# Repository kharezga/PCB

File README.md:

# My PCBs
This repository contains sereveral PCB board that I've design for use in the Formula Student racecar. In addition to PCB designs, the repository also includes 3D models of some of their housings.

## 🚨 Tractive System Active Light (TSAL) module 🚨
According to the Formula Student Rules 2022, the Tractive System Active Light (TSAL) is a safety feature that must be implemented in all electric vehicles participating in the competition. Whole project of the TSAL can be found in this repository, including PCB layout and scheme. 

### Overview
The TSAL must be based on the voltage level of the High Voltage (HV) battery or the voltage level of the motor controller, and it should indicate whether the tractive system is active or not.

The TSAL should be mounted on the rear of the vehicle and must be clearly visible from the rear of the vehicle during both day and night conditions. The light should be red or yellow and must flash at a frequency between 1Hz and 4Hz.

During normal operation, the TSAL should remain on steadily to indicate that the tractive system is active. When the vehicle is in an emergency or shutdown state, the TSAL should flash at a higher frequency between 4Hz and 10Hz to indicate that the tractive system is inactive.

## Ready-to-Run Sound and Autonomous System Status Indicators module
In this repository there is also a project containing a module for ready-to-run-sound and ASSI safety systems.

### 🔊 Ready-to-Run Sound 🔊
According to the Formula Student Rules 2022, Ready-to-Run Sound (RtRS) is a safety feature that must be implemented in all electric vehicles participating in the competition.

The purpose of the RtRS is to alert pedestrians and other drivers of the presence of an electric vehicle, which can be difficult to hear due to its quiet operation. The sound must be continuous, with a minimum sound pressure level of 55dB(A) and a maximum of 75dB(A) measured at a distance of 2 meters from the vehicle in all directions.

The RtRS must be activated when the vehicle is in Ready-to-Run mode, which means the vehicle is ready to move and all systems are operational. The sound should be automatically turned off when the vehicle is not in Ready-to-Run mode or is turned off.

### 🤖 Autonomous System Status Indicators 🤖
According to the Formula Student Rules 2022, the Autonomous System Status Indicators (ASSI) module is a safety feature that must be implemented in all autonomous vehicles participating in the competition.

The ASSI module is responsible for providing visual and audible feedback on the status of the autonomous system to the vehicle occupants, other drivers, and pedestrians. The module must be integrated into the vehicle's user interface or dashboard and should display the following information:

+ Autonomous System Status: The module must display the status of the autonomous system, indicating whether it is active or inactive.
+ System Health Status: The module must display the health status of the autonomous system, indicating whether the system is functioning correctly or not.
+ System State: The module must display the current state of the autonomous system, indicating whether the system is in calibration mode, initialization mode, or autonomous driving mode.

In addition to the visual feedback, the ASSI module must also provide audible feedback to alert the vehicle occupants and pedestrians of any critical issues related to the autonomous system. The audible feedback must be distinct and easily identifiable from any other sounds in the vehicle or surrounding environment.

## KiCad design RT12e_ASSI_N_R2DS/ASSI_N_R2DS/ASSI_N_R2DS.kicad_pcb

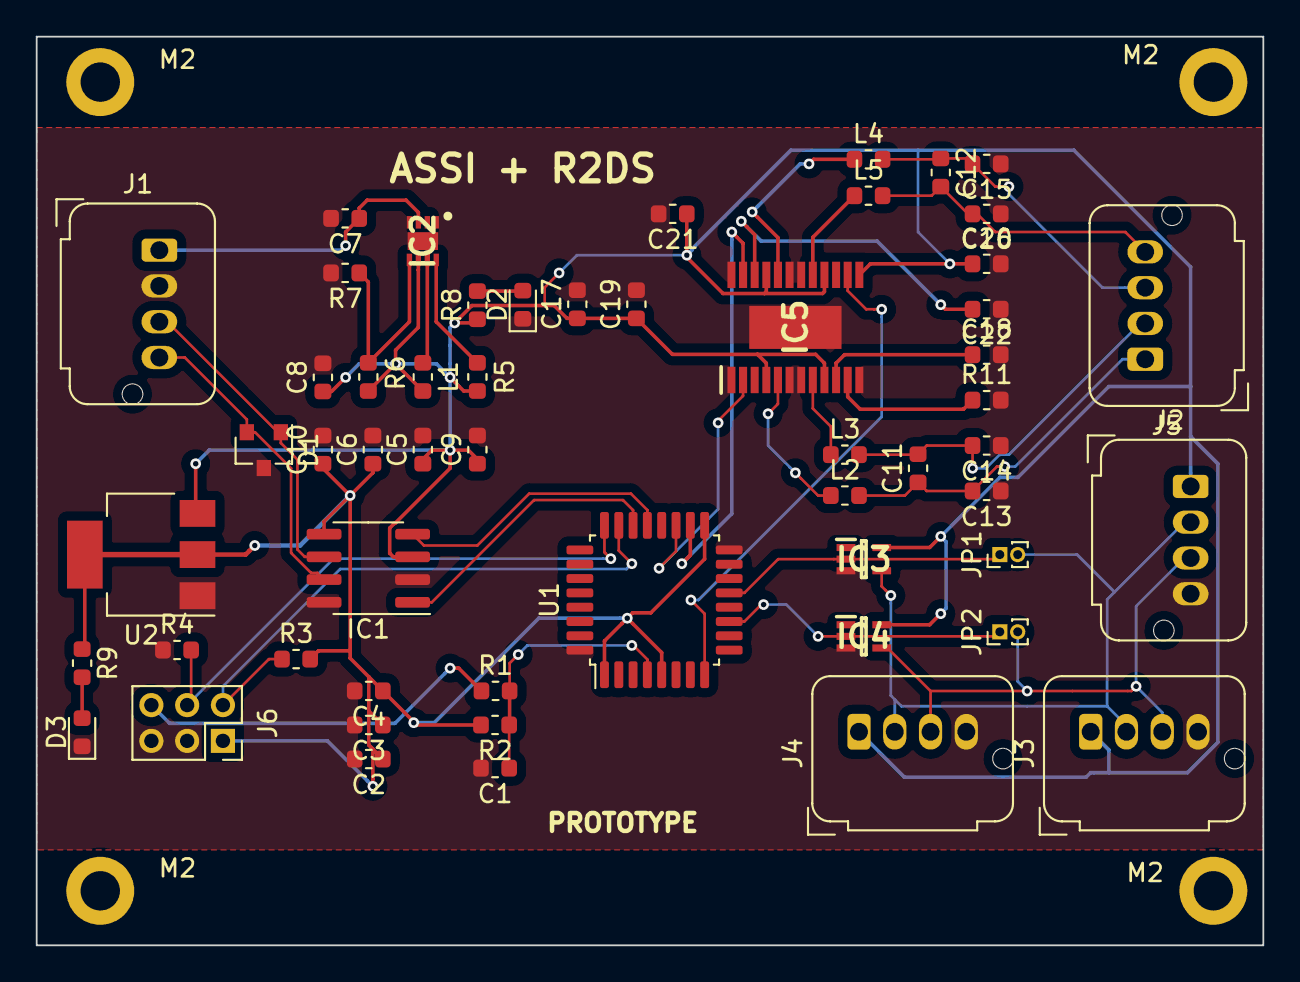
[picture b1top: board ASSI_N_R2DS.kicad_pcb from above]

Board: 2 copper layers, 68.6 x 50.8 mm, 59 parts (0 on the bottom side), 35 nets.

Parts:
C1, C2, C3, C4, C5, C6, C13, C14, C15, C16: 100nF; C_0603_1608Metric
C7: 10nF; C_0603_1608Metric
C8: 22nF; C_0603_1608Metric
C9, C10, C17, C20, C21, C22: 1uF; C_0603_1608Metric
C11, C12: 0.47uF; C_0603_1608Metric
C18: 220pF; C_0603_1608Metric
C19: 10uF; C_0603_1608Metric
D1: NUP2105L; SOT-23
D2, D3: LED; LED_0603_1608Metric
IC1: IC_CAN-TRANSCEIVER_TLE7250XSJ-Racing_symbols; SOIC-8_3.9x4.9mm_P1.27mm
IC2: TPS62160QDSGRQ1; SON50P200X200X80-9N
IC3, IC4: 74LV1T04GW-Q100H; SOT65P212X110-5N
IC5: TPA2008D2PWPR; SOP65P640X120-25N
J1: CAN; JST_JWPF_B04B-JWPF-SK-R_1x04_P2.00mm_Vertical
J2: OUT_LED1; JST_JWPF_B04B-JWPF-SK-R_1x04_P2.00mm_Vertical
J3: OUT_LED2; JST_JWPF_B04B-JWPF-SK-R_1x04_P2.00mm_Vertical
J4: OUT_LED3; JST_JWPF_B04B-JWPF-SK-R_1x04_P2.00mm_Vertical
J5: OUT_SPEAKER; JST_JWPF_B04B-JWPF-SK-R_1x04_P2.00mm_Vertical
J6: SWD; PinSocket_2x03_P2.00mm_Vertical
JP1, JP2: Jumper; PinHeader_1x02_P1.00mm_Vertical
L1: 2.2uH; L_0603_1608Metric
L2, L3, L4, L5: 33uH; L_0603_1608Metric
M2, M2#2, M2#3, M2#4: MountingHole_2.2mm_M2_ISO14580_Pad
R1: 100; R_0603_1608Metric
R2: 10K; R_0603_1608Metric
R3, R4: 10k; R_0603_1608Metric
R5: 100k; R_0603_1608Metric
R6: 680k; R_0603_1608Metric
R7: 130k; R_0603_1608Metric
R8, R9: 1k; R_0603_1608Metric
R11: 120K; R_0603_1608Metric
U1: STM32F042K6Tx; LQFP-32_7x7mm_P0.8mm
U2: AP7313-33SRG-7; SOT-223-3_TabPin2

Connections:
+3V3: C2.1, C3.1, C4.1, C6.1, C10.1, IC1.5, J6.1, R2.2, R3.2, R9.1, U1.1, U1.5, U1.17, U2.2
+5V: C5.1, C8.1, C9.1, C17.1, C19.1, C20.1, C21.1, IC1.3, IC2.6, IC3.5, IC4.5, IC5.4, IC5.9, IC5.13, IC5.16, IC5.21, J2.1, J3.1, J4.1, L1.2, R5.1, R6.1, R8.1, U2.3
/CAN/CAN_H: D1.2, IC1.7, J1.4
/CAN/CAN_L: D1.1, IC1.6, J1.3
/CAN/CAN_RX: IC1.4, U1.21
/CAN/CAN_TX: IC1.1, U1.22
/LC_FILTER/L+: C11.1, C13.2, J5.1, L2.2
/LC_FILTER/L-: C11.2, C14.2, J5.2, L3.2
/LC_FILTER/LIN+: IC5.5, L2.1
/LC_FILTER/LIN-: IC5.8, L3.1
/LC_FILTER/R+: C12.1, C15.2, J5.3, L4.2
/LC_FILTER/R-: C12.2, C16.2, J5.4, L5.2
/LC_FILTER/RIN+: IC5.20, L4.1
/LC_FILTER/RIN-: IC5.17, L5.1
/LED/LED_MOSI: IC3.4, J2.2, J3.2, J4.2, JP1.2
/LED/LED_SCK: IC4.4, J2.3, J3.3, J4.3, JP2.2
/LED/MOSI: IC3.2, JP1.1, U1.13
/LED/SCK: IC4.2, JP2.1, U1.11
/POWER_SUPPLY/VIN: C7.1, IC2.2, IC2.3, J1.1
/STM32/AMP_L_CHANNEL: IC5.2, U1.19
/STM32/AMP_R_CHANNEL: IC5.23, U1.18
/STM32/AMP_VOLUME: IC5.14, U1.8
/SWDIO/MCU_RESET: J6.6, R1.1
/SWDIO/MCU_SWCLK: J6.4, R4.2, U1.24
/SWDIO/MCU_SWDIO: J6.2, R3.1, U1.23
GND: C1.2, C2.2, C3.2, C4.2, C5.2, C6.2, C7.2, C8.2, C9.2, C10.2, C13.1, C14.1, C15.1, C16.1, C17.2, C18.2, C19.2, C20.2, C21.2, C22.1, D1.3, D2.1, D3.1, IC1.2, IC1.8, IC2.1, IC2.4, IC2.9, IC3.3, IC4.3, IC5.1, IC5.6, IC5.7, IC5.12, IC5.18, IC5.19, IC5.24, IC5.25, J1.2, J2.4, J3.4, J4.4, J6.3, J6.5, R4.1, R7.2, R11.2, U1.16, U1.32, U2.1
unnamed: C1.1, R1.2, R2.1, U1.4
unnamed: C18.1, IC5.10
unnamed: C22.2, IC5.22
unnamed: D2.2, R8.2
unnamed: D3.2, R9.2
unnamed: IC2.5, R6.2, R7.1
unnamed: IC2.7, L1.1
unnamed: IC2.8, R5.2
unnamed: IC5.11, R11.1

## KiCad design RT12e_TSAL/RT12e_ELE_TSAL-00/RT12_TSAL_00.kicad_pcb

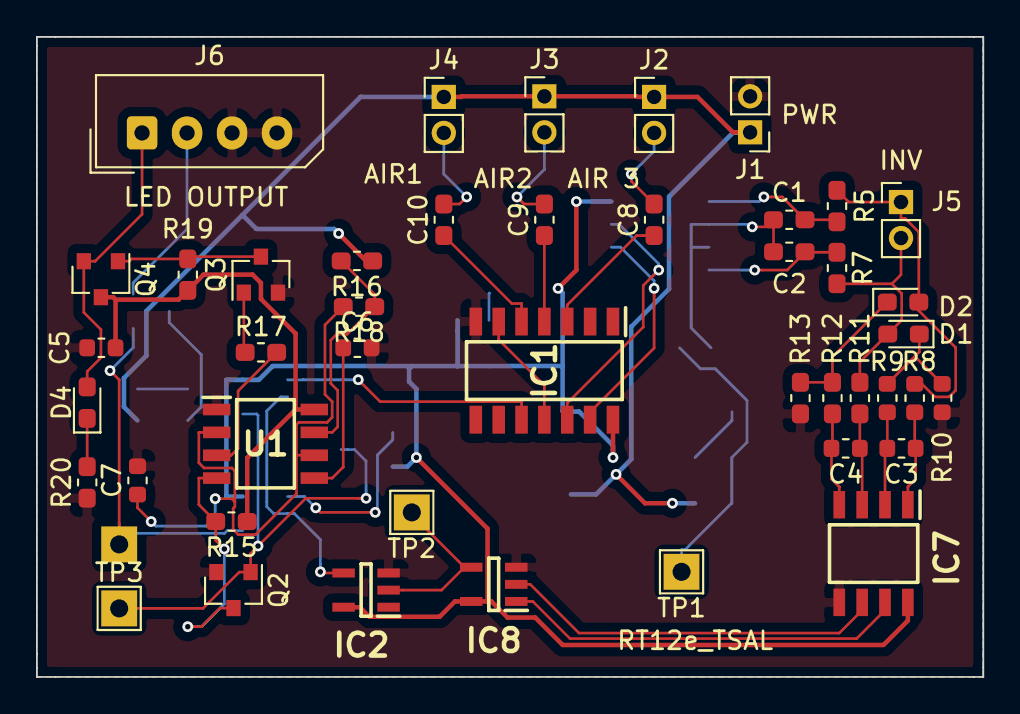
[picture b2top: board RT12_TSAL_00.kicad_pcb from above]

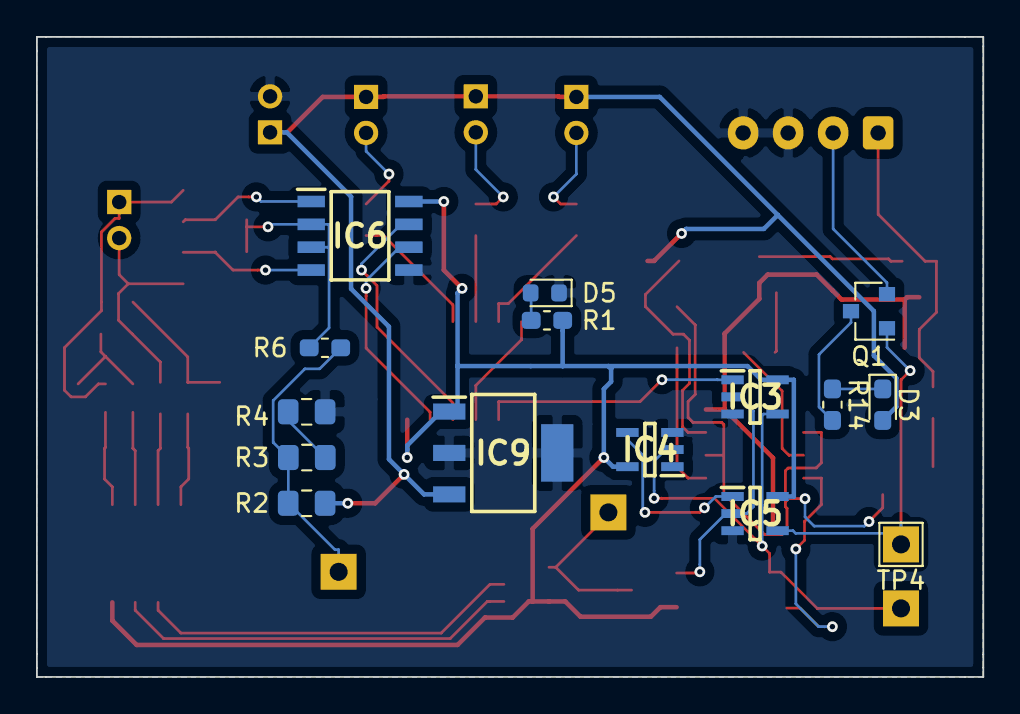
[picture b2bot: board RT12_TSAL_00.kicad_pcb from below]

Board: 2 copper layers, 52.6 x 35.6 mm, 59 parts (15 on the bottom side), 46 nets.

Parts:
C1, C2: CC_0603_10nF_14V; C_0603_1608Metric_Pad1.05x0.95mm_HandSolder
C3, C4: CC_0603_10nF_14V; C_0603_1608Metric
C5, C6: CC_0603_100nF_14V; C_0603_1608Metric
C7: CC_0603_1uF_14V; C_0603_1608Metric
C8, C9, C10: 100n; C_0603_1608Metric_Pad1.05x0.95mm_HandSolder
D1: 0.2V; D_0603_1608Metric_Pad1.05x0.95mm_HandSolder
D2: 0.2; D_0603_1608Metric_Pad1.05x0.95mm_HandSolder
D3: D_LED_0603_GREEN_20mA; D_0603_1608Metric_Pad1.05x0.95mm_HandSolder
D4: D_LED_0603_RED_20mA; D_0603_1608Metric_Pad1.05x0.95mm_HandSolder
D5: VCC; LED_0603_1608Metric
IC1: 74HCT4075D,653; SOIC127P600X175-14N
IC2, IC4: 74HC1G04GV-Q100H_INV; SOT95P275X110-5N
IC3, IC5, IC8: 74LV1T08GVH_AND; SOT95P275X110-5N
IC6, IC7: LT1720CS8#PBF; SOIC127P599X175-8N
IC9: ZSR500GTA; SOT230P700X180-4N
J1: LVS; PinHeader_1x02_P2.00mm_Vertical
J2: AIR1; PinHeader_1x02_P2.00mm_Vertical
J3: AIR2; PinHeader_1x02_P2.00mm_Vertical
J4: AIR_PRE; PinHeader_1x02_P2.00mm_Vertical
J5: BATT_n_INV; PinHeader_1x02_P2.00mm_Vertical
J6: INDICATOR_LED; Molex_SPOX_5267-04A_1x04_P2.50mm_Vertical
Q1, Q2, Q3: BSS123; SOT-23
Q4: BSS84; SOT-23
R1: R_0603_1K_5%; R_0603_1608Metric_Pad1.05x0.95mm_HandSolder
R2: R_0805_2320_1%; R_0805_2012Metric_Pad1.15x1.40mm_HandSolder
R3, R4: R_0805_575_1%; R_0805_2012Metric_Pad1.15x1.40mm_HandSolder
R5, R6, R7, R11, R12: R_0603_100_1%; R_0603_1608Metric_Pad1.05x0.95mm_HandSolder
R8, R9: R_0603_100_1%; R_0603_1608Metric
R10: R_0603_10K_1%; R_0603_1608Metric
R13: R_0603_10K_1%; R_0603_1608Metric_Pad1.05x0.95mm_HandSolder
R14, R20: R_0603_2K2_5%; R_0603_1608Metric_Pad1.05x0.95mm_HandSolder
R15, R16: R_0603_22K_5%; R_0603_1608Metric_Pad1.05x0.95mm_HandSolder
R17: R_0603_47_5%; R_0603_1608Metric_Pad1.05x0.95mm_HandSolder
R18: R_0603_220K_5%; R_0603_1608Metric_Pad1.05x0.95mm_HandSolder
R19: R_0603_10K_5%; R_0603_1608Metric_Pad1.05x0.95mm_HandSolder
TP1: Vref; TestPoint_THTPad_2.0x2.0mm_Drill1.0mm
TP2: TS_Error; TestPoint_THTPad_2.0x2.0mm_Drill1.0mm
TP3: RED; TestPoint_THTPad_2.0x2.0mm_Drill1.0mm
TP4: GRN; TestPoint_THTPad_2.0x2.0mm_Drill1.0mm
U1: NE555; NE555DR

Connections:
+5V: IC1.14, IC2.5, IC3.5, IC4.5, IC5.5, IC6.8, IC7.8, IC8.5, IC9.1, R1.1
+12V: C5.1, D3.2, IC9.3, J1.1, J2.1, J3.1, J4.1, Q4.3, R2.1, R15.1, R16.1, R19.1, U1.8
/Implausiility Detection/ANALOG_BATT: D1.2, J5.1, R5.2, R8.2
/Implausiility Detection/ANALOG_INV: D2.2, J5.2, R7.2, R11.2
/Implausiility Detection/TS_ERROR: IC2.2, IC8.4, TP2.1
/Implausiility Detection/U_BATT: IC1.12, IC6.7
/Implausiility Detection/U_INV: IC1.13, IC6.6
/Implausiility Detection/U_ref: R2.2, R3.1, R6.1, TP1.1
/LEDS/GREEN: IC5.4, Q1.1, TP4.1
/LEDS/GRN+: J6.2, Q1.2
/LEDS/RED: IC3.4, IC4.2, Q2.1, TP3.1
/LEDS/RED+: D4.2, J6.1, Q4.2
GND: C5.2, C6.2, C7.2, D5.1, IC1.7, IC2.3, IC3.3, IC4.3, IC5.3, IC6.5, IC7.5, IC8.3, IC9.2, IC9.4, J1.2, J6.3, J6.4, Q2.2, Q3.2, R4.2, R10.2, R13.2, R20.1, U1.1
unnamed: C1.1, IC6.1, R5.1
unnamed: C1.2, C2.1, IC6.2, IC6.3, R6.2
unnamed: C2.2, IC6.4, R7.1
unnamed: C3.1, IC7.1, R8.1
unnamed: C3.2, IC7.2, R9.2
unnamed: C4.1, IC7.3, R11.1
unnamed: C4.2, IC7.4, R12.2
unnamed: C6.1, U1.5
unnamed: C7.1, R18.2, U1.2, U1.6
unnamed: C8.1, IC1.3
unnamed: C8.2, J2.2
unnamed: C9.1, IC1.4
unnamed: C9.2, J3.2
unnamed: C10.1, IC1.5
unnamed: C10.2, J4.2
unnamed: D1.1, R12.1, R13.1
unnamed: D2.1, R9.1, R10.1
unnamed: D3.1, R14.1
unnamed: D4.1, R20.2
unnamed: D5.2, R1.2
unnamed: IC1.10, IC3.1
unnamed: IC1.6, IC1.11
unnamed: IC2.4, IC3.2, IC5.2
unnamed: IC4.4, IC5.1
unnamed: IC7.6, IC8.2
unnamed: IC7.7, IC8.1
unnamed: Q1.3, R14.2
unnamed: Q2.3, R15.2, U1.4
unnamed: Q3.1, R17.1
unnamed: Q3.3, Q4.1, R19.2
unnamed: R3.2, R4.1
unnamed: R16.2, R18.1, U1.7
unnamed: R17.2, U1.3

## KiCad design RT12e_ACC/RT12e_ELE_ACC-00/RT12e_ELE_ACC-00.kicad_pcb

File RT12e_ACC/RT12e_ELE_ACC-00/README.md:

# RT12e_ELE_ACC_00
Projekt w kiCad'ie 5.1.8
Całość jest takze w pdf'ie w docs.

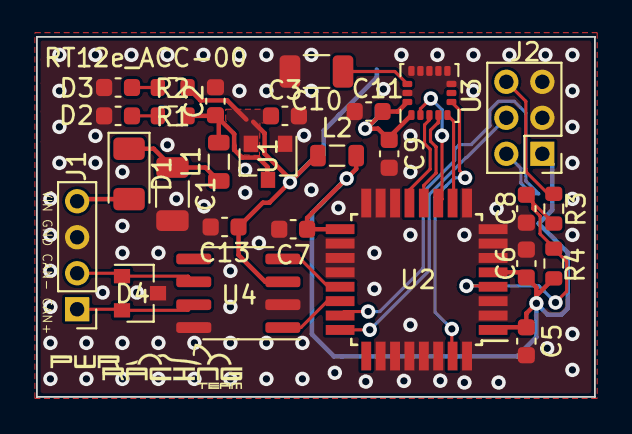
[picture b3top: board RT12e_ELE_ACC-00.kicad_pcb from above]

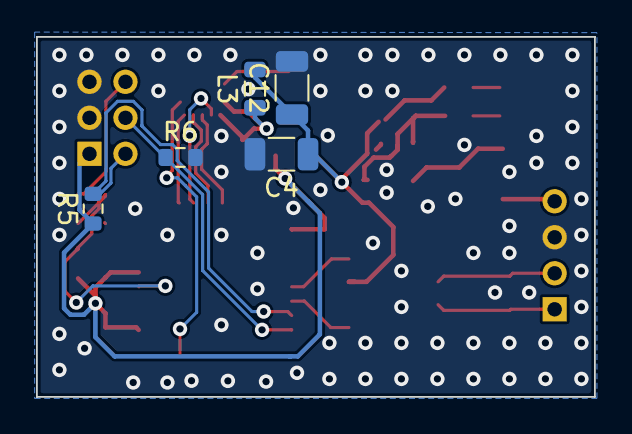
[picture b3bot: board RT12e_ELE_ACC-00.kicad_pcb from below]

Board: 2 copper layers, 31.0 x 20.0 mm, 33 parts (5 on the bottom side), 23 nets.

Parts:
C1, C12: 10uF; C_1206_3216Metric
C2, C3, C5, C6, C7, C8, C9, C11, C13: 100nF; C_0603_1608Metric
C4: 1uF; C_1206_3216Metric
C10: 0.47uF; C_1206_3216Metric
D1: D; D_1206_3216Metric
D2, D3: D; C_0603_1608Metric
D4: NUP2105L; SOT-23
J1: 5V_CAN; PinHeader_1x04_P2.00mm_Vertical
J2: SWD; PinHeader_2x03_P2.00mm_Vertical
L1, L2, L3: L; L_0805_2012Metric
R1: 270; R_0603_1608Metric
R2: 150; R_0603_1608Metric
R3: 100; R_0603_1608Metric
R4, R5, R6: 10K; R_0603_1608Metric
Ref**: Val**; PWR_logo_11x2,5
U1: LM1085-3.3; SOT-23
U2: STM32F042K6Tx; TQFP-32_7x7mm_P0.8mm
U3: IAM-20680; LGA-16_3x3mm_P0.5mm_LayoutBorder3x5y
U4: SN65HVD230; SOIC-8_3.9x4.9mm_P1.27mm

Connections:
+3V3: C3.1, C4.1, C12.1, C13.1, L2.1, L3.2, R2.1, U1.2, U4.3
+5V: C2.1, L1.2, R1.1, U1.3
/CAN+: D4.2, J1.1, U4.7
/CAN-: D4.1, J1.2, U4.6
/CAN/CAN_RX: U2.21, U4.4
/CAN/CAN_TX: U2.22, U4.1
/IAM-20680/ACC_V+: C9.1, C11.1, L3.1, U3.1, U3.16
/IAM-20680/CS: U2.10, U3.5
/IAM-20680/REGOUT: C10.1, U3.14
/IAM-20680/SDI: U2.13, U3.3
/IAM-20680/SDO: U2.12, U3.4
/IAM-20680/SPC: U2.11, U3.2
/STM32/DI_IAM_INT: U2.31, U3.6
/STM32/RESET: J2.6, R3.2
/STM32/STM_RESET: C8.1, R3.1, R4.2, U2.4
/STM32/STM_V+: C5.1, C6.1, C7.1, J2.1, L2.2, R4.1, R5.1, U2.1, U2.5, U2.17
/STM32/SWCLK: J2.4, R6.1, U2.24
/SWD_connect.sch/SDWIO: J2.2, R5.2, U2.23
/VIN: D1.2, J1.4
GND: C1.2, C2.2, C3.2, C4.2, C5.2, C6.2, C7.2, C8.2, C9.2, C10.2, C11.2, C12.2, C13.2, D2.1, D3.1, D4.3, J1.3, J2.3, J2.5, R6.2, U1.1, U2.2, U2.3, U2.6, U2.7, U2.8, U2.9, U2.14, U2.15, U2.16, U2.18, U2.19, U2.20, U2.26, U2.27, U2.28, U2.29, U2.30, U2.32, U3.8, U3.9, U3.10, U3.11, U3.12, U3.13, U3.15, U4.2, U4.8
unnamed: C1.1, D1.1, L1.1
unnamed: D2.2, R1.2
unnamed: D3.2, R2.2

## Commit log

2022-02-03 Projects init
